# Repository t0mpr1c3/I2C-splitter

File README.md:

I2C-splitter
============

1-3 I2C splitter.

Released under the [Creative Commons License Attribution-ShareAlike 3.0](http://creativecommons.org/licenses/by-sa/3.0/)

Version history
---------------

_IS01_

First version.

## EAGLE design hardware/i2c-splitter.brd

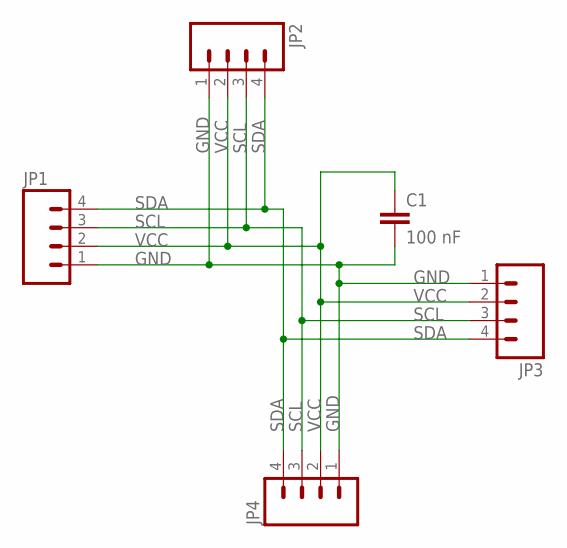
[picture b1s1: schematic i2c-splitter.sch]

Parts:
C1: 100 nF; C0805
JP1, JP2, JP3, JP4: M04PTH; 1X04

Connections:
GND: C1.2, JP1.1, JP2.1, JP3.1, JP4.1
SCL: JP1.3, JP2.3, JP3.3, JP4.3
SDA: JP1.4, JP2.4, JP3.4, JP4.4
VCC: C1.1, JP1.2, JP2.2, JP3.2, JP4.2

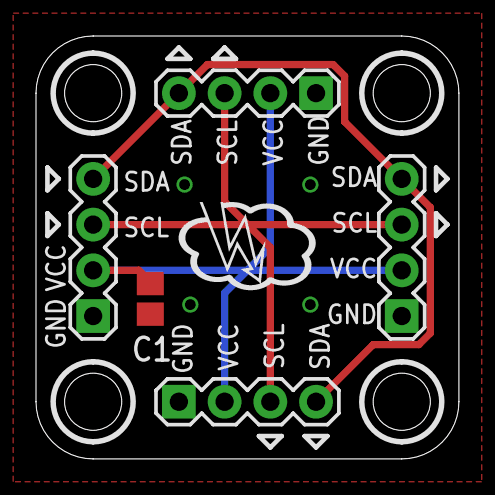
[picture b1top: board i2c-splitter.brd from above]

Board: 4 copper layers, 23.5 x 23.5 mm, 6 parts (1 on the bottom side), 4 nets.

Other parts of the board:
U$1: OSHW-LOGO-S

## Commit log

2013-11-18 reversed headers
2013-11-20 optional bypass capacitor
2013-11-20 stop mask over vias
2013-11-26 tweak gerbers
2013-12-03 IS01 for Seeedstudio
2013-12-24 IS01 Elecrow order
2014-01-30 IS01 .png files, removed gerbers

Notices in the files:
hardware/i2c-splitter.brd:
CC BY-SA 3.0
parts and their libraries:
SparkFun: Licensing: CC v3.0 Share-Alike You are welcome to use this library for commercial purposes.
